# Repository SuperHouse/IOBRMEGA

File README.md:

I/O Breakout Shield (Mega)
==========================
Copyright 2017 SuperHouse Automation Pty Ltd  
SuperHouse site:  <www.superhouse.tv>  

Breaks out sets of I/O pins to 2x6 pin headers.

Features:

 * 8 x 2x6 shrouded pin headers
 * Each header provides 8 x data lines, GND, VIN, IOREF, and RESET

More information is available at:

  http://www.superhouse.tv/iobrmega

INSTALLATION
------------
The design is saved as an EAGLE project. EAGLE PCB design software is
available from www.cadsoftusa.com free for non-commercial use. To use
this project download it and place the directory containing these files
into the "eagle" directory on your computer. Then open EAGLE and
navigate to the project.

DISTRIBUTION
------------
The specific terms of distribution of this project are governed by the
license referenced below.

LICENSE
-------
Licensed under the TAPR Open Hardware License (www.tapr.org/OHL).
The "license" folder within this repository also contains a copy of
this license in plain text format.

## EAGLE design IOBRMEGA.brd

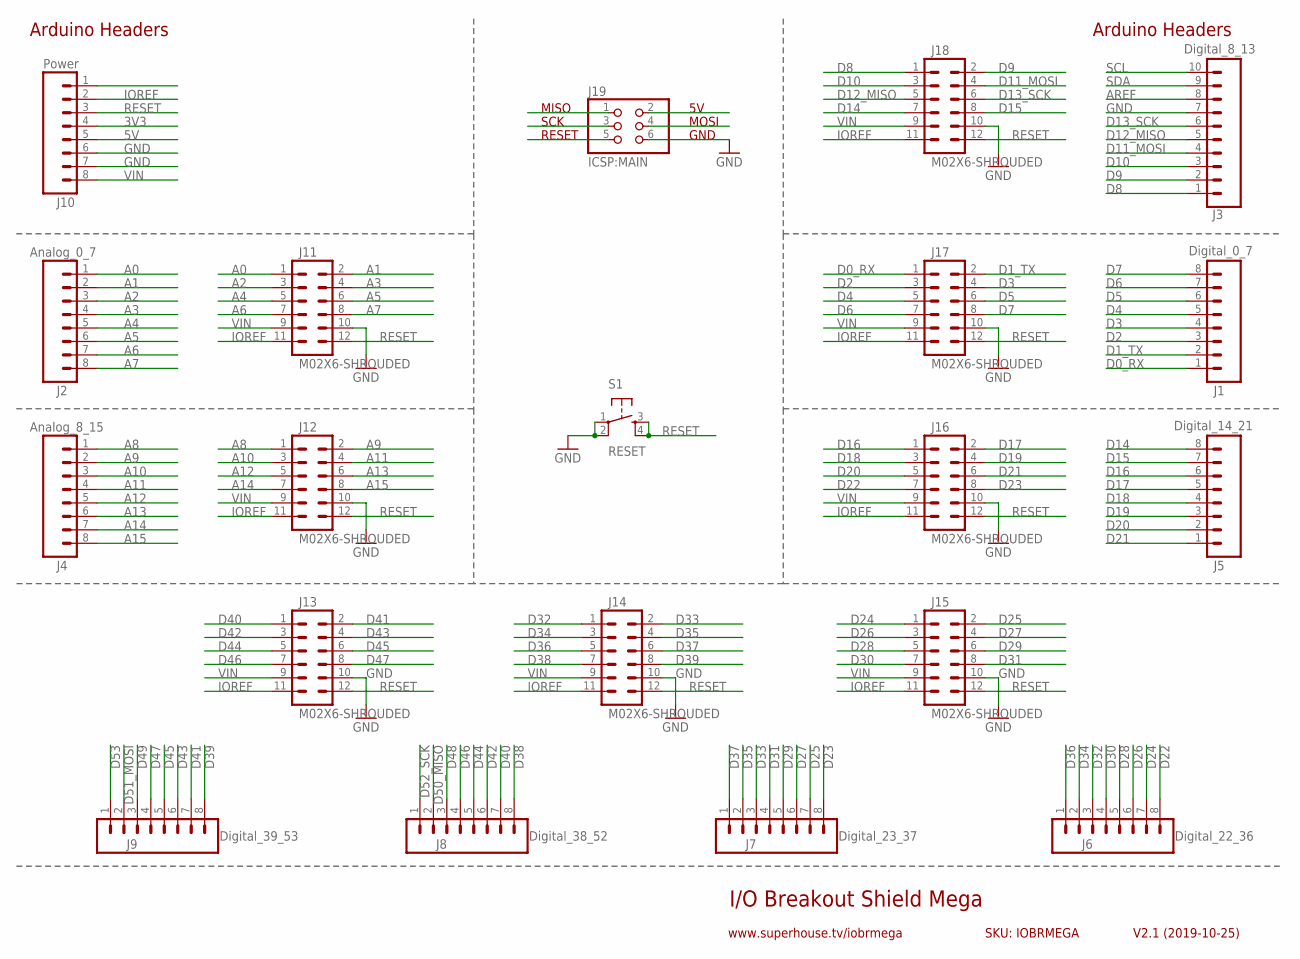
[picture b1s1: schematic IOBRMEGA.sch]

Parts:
J1: Digital_0_7; 1X08-P-BELOW
J2: Analog_0_7; 1X08-P-BELOW
J3: Digital_8_13; 1X10-P-BELOW
J4: Analog_8_15; 1X08-P-BELOW
J5: Digital_14_21; 1X08-P-BELOW
J6: Digital_22_36; 1X08-P-BELOW
J7: Digital_23_37; 1X08-P-BELOW
J8: Digital_38_52; 1X08-P-BELOW
J9: Digital_39_53; 1X08-P-BELOW
J10: Power; 1X08-P-BELOW
J11, J12, J13, J14, J15, J16, J17, J18: M02X6-SHROUDED; 2X06-SHROUDED
J19: ICSP:MAIN; 2X03
S1: RESET; TACTILE-PTH-6MM

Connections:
3V3: J10.4
5V: J10.5
A0: J2.1, J11.1
A1: J2.2, J11.2
A2: J2.3, J11.3
A3: J2.4, J11.4
A4: J2.5, J11.5
A5: J2.6, J11.6
A6: J2.7, J11.7
A7: J2.8, J11.8
A8: J4.1, J12.1
A9: J4.2, J12.2
A10: J4.3, J12.3
A11: J4.4, J12.4
A12: J4.5, J12.5
A13: J4.6, J12.6
A14: J4.7, J12.7
A15: J4.8, J12.8
AREF: J3.8
D0_RX: J1.1, J17.1
D1_TX: J1.2, J17.2
D2: J1.3, J17.3
D3: J1.4, J17.4
D4: J1.5, J17.5
D5: J1.6, J17.6
D6: J1.7, J17.7
D7: J1.8, J17.8
D8: J3.1, J18.1
D9: J3.2, J18.2
D10: J3.3, J18.3
D11_MOSI: J3.4, J18.4
D12_MISO: J3.5, J18.5
D13_SCK: J3.6, J18.6
D14: J5.8, J18.7
D15: J5.7, J18.8
D16: J5.6, J16.1
D17: J5.5, J16.2
D18: J5.4, J16.3
D19: J5.3, J16.4
D20: J5.2, J16.5
D21: J5.1, J16.6
D22: J6.8, J16.7
D23: J7.8, J16.8
D24: J6.7, J15.1
D25: J7.7, J15.2
D26: J6.6, J15.3
D27: J7.6, J15.4
D28: J6.5, J15.5
D29: J7.5, J15.6
D30: J6.4, J15.7
D31: J7.4, J15.8
D32: J6.3, J14.1
D33: J7.3, J14.2
D34: J6.2, J14.3
D35: J7.2, J14.4
D36: J6.1, J14.5
D37: J7.1, J14.6
D38: J8.8, J14.7
D39: J9.8, J14.8
D40: J8.7, J13.1
D41: J9.7, J13.2
D42: J8.6, J13.3
D43: J9.6, J13.4
D44: J8.5, J13.5
D45: J9.5, J13.6
D46: J8.4, J13.7
D47: J9.4, J13.8
D48: J8.3
D49: J9.3
D50_MISO: J8.2
D51_MOSI: J9.2
D52_SCK: J8.1
D53: J9.1
GND: J3.7, J10.6, J10.7, J11.10, J12.10, J13.10, J14.10, J15.10, J16.10, J17.10, J18.10, J19.6, S1.1, S1.2
IOREF: J10.2, J11.11, J12.11, J13.11, J14.11, J15.11, J16.11, J17.11, J18.11
RESET: J10.3, J11.12, J12.12, J13.12, J14.12, J15.12, J16.12, J17.12, J18.12, S1.3, S1.4
SCL: J3.10
SDA: J3.9
VIN: J10.8, J11.9, J12.9, J13.9, J14.9, J15.9, J16.9, J17.9, J18.9

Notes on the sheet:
I/O Breakout Shield Mega
V2.1 (2019-10-25)
www.superhouse.tv/iobrmega
SKU: IOBRMEGA
Arduino Headers
GND
MISO
RESET
SCK
MOSI

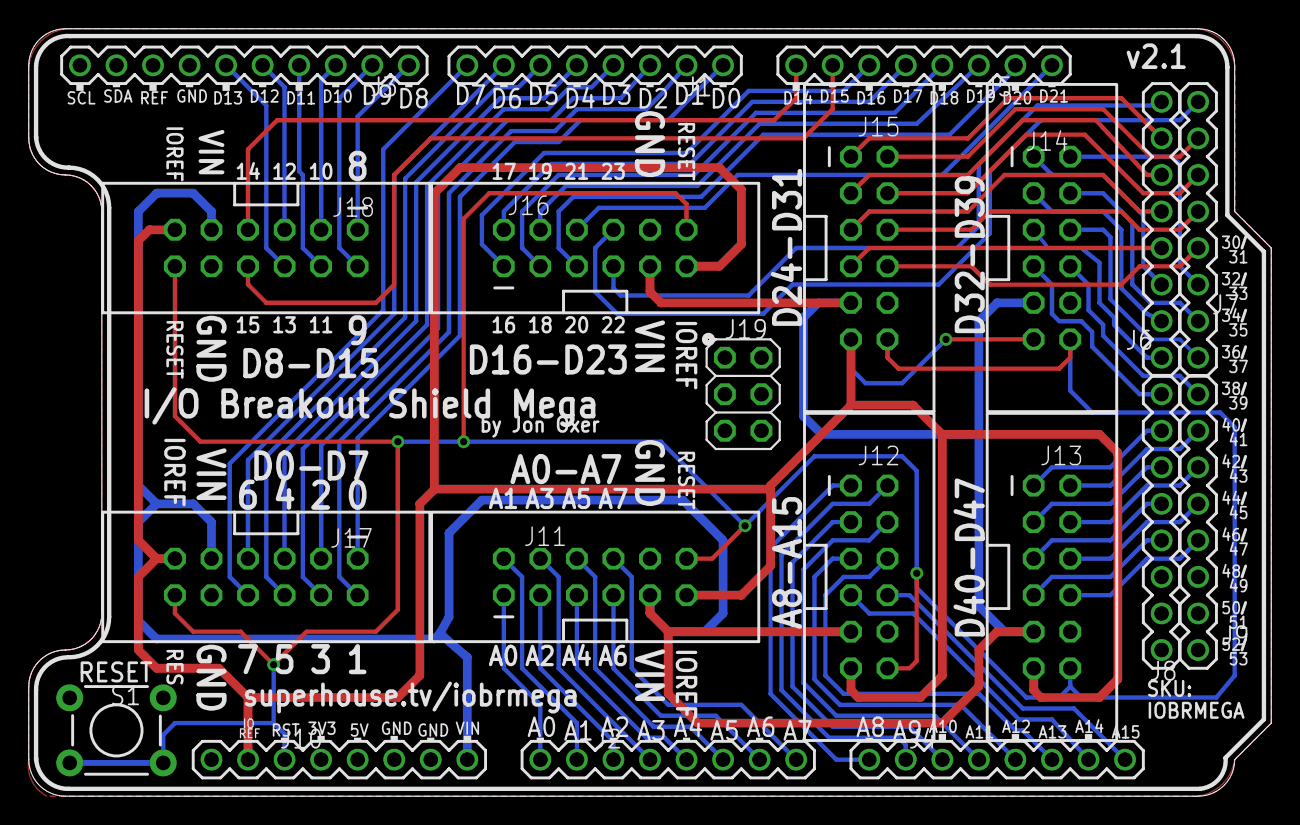
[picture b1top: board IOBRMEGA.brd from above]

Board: 2 copper layers, 86.4 x 53.3 mm, 20 parts (0 on the bottom side), 68 nets.

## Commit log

2017-07-21 Initial project import
2017-07-24 Expanded headers to 2x6 to include IOREF and RESET for v2.0 release
2017-07-24 Updated docs for v2.0 release
2019-07-18 Part swap to SuperHouse library to add 3D models
2019-10-25 Updated for v2.1 release
2019-10-26 Final tweaks for v2.1 release
2019-10-26 Scaled down image

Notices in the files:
IOBRMEGA.brd:
(C)2017-2019 SuperHouse Automation Pty Ltd
Open Hardware License
